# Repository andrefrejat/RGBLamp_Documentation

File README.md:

# RGBLamp_Documentation
RGB Lamp made beggining 2015. The base is an arduino Uno. Software and hardware explanation on the video (in portuguese).

The project works in three different forms:
1) Red green and blue lights alternate
2) The ammount of Red Green and Blue on the light is controlled by three potentiometers on the side
3) The color is controlled via computer software.

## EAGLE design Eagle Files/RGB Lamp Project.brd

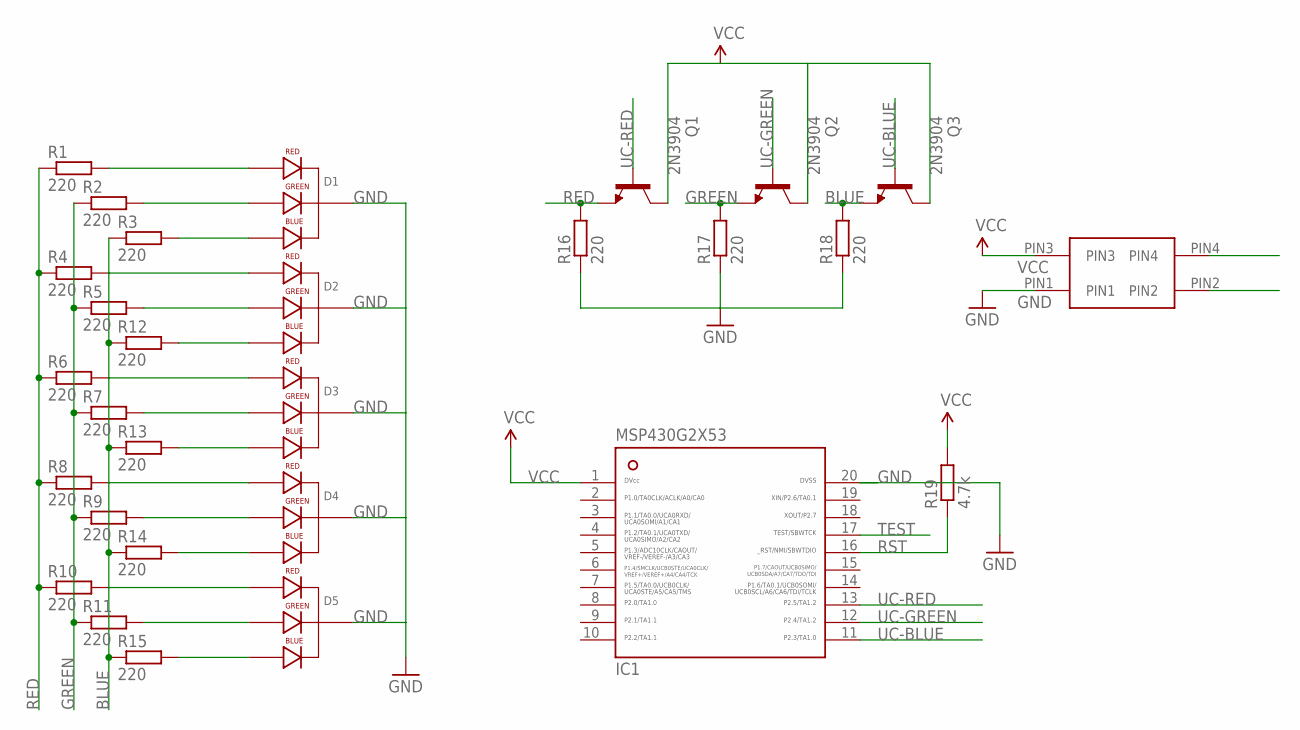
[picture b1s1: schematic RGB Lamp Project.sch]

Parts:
D1, D2, D3, D4, D5: LED-RGB-CC-THRUCLEAR; LED-RGB-THRU
IC1: MSP430G2X53-20PW20; PW20
Q1, Q2, Q3: 2N3904; TO92
R1, R2, R3, R4, R5, R6, R7, R8, R9, R10, R11, R12, R13, R14, R15, R16, R17, R18: 220; R0805
R19: 4.7k; R0805
U$1: PINHEADER-2X2-SMD

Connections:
BLUE: Q3.3 (E), R3.1, R12.1, R13.1, R14.1, R15.1, R18.2
GND: D1.2 (CATHODE), D2.2 (CATHODE), D3.2 (CATHODE), D4.2 (CATHODE), D5.2 (CATHODE), IC1.20, R16.1, R17.1, R18.1, U$1.PIN1
GREEN: Q2.3 (E), R2.1, R5.1, R7.1, R9.1, R11.1, R17.2
unnamed: D1.1 (RED_CATHODE), R1.2
unnamed: D1.3 (GREEN_CATHODE), R2.2
unnamed: D1.4 (BLUE_CATHODE), R3.2
unnamed: D2.1 (RED_CATHODE), R4.2
unnamed: D2.3 (GREEN_CATHODE), R5.2
unnamed: D2.4 (BLUE_CATHODE), R12.2
unnamed: D3.1 (RED_CATHODE), R6.2
unnamed: D3.3 (GREEN_CATHODE), R7.2
unnamed: D3.4 (BLUE_CATHODE), R13.2
unnamed: D4.1 (RED_CATHODE), R8.2
unnamed: D4.3 (GREEN_CATHODE), R9.2
unnamed: D4.4 (BLUE_CATHODE), R14.2
unnamed: D5.1 (RED_CATHODE), R10.2
unnamed: D5.4 (BLUE_CATHODE), R15.2
unnamed: D5.3 (GREEN_CATHODE), R11.2
RED: Q1.3 (E), R1.1, R4.1, R6.1, R8.1, R10.1, R16.2
RST: IC1.16, R19.1, U$1.PIN4
TEST: IC1.17, U$1.PIN2
UC-BLUE: IC1.11, Q3.2 (B)
UC-GREEN: IC1.12, Q2.2 (B)
UC-RED: IC1.13, Q1.2 (B)
VCC: IC1.1, Q1.1 (C), Q2.1 (C), Q3.1 (C), R19.2, U$1.PIN3

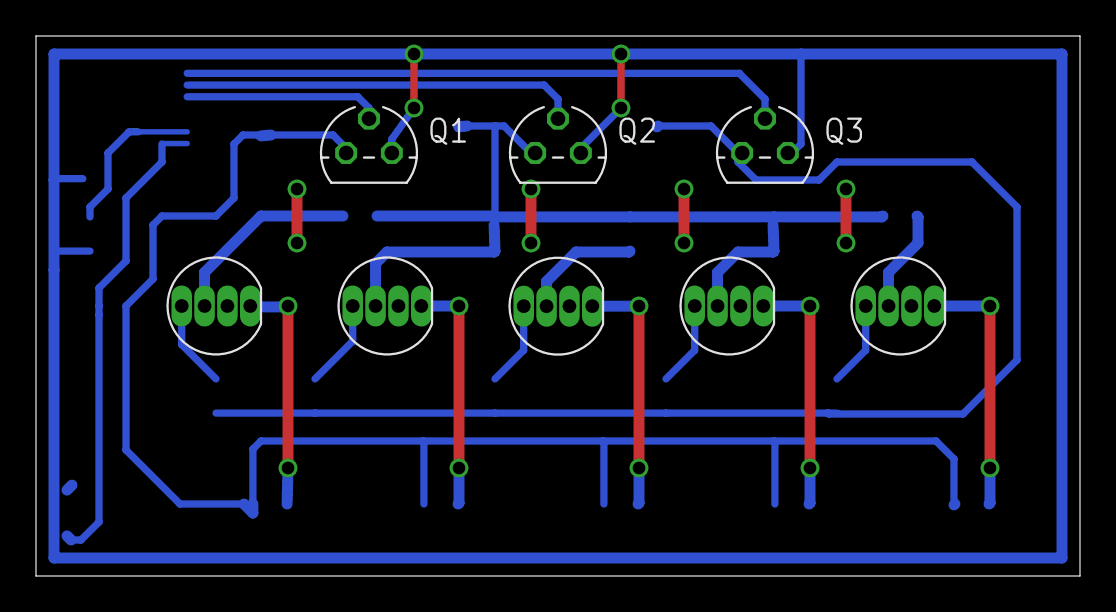
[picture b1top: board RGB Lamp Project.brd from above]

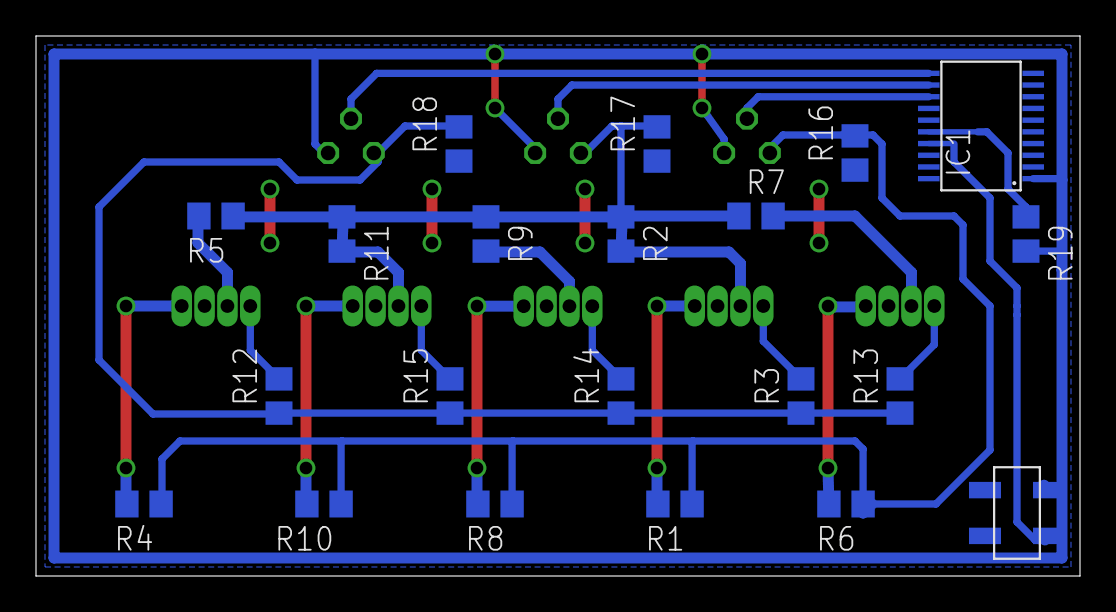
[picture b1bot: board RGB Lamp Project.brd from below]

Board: 2 copper layers, 58.0 x 30.0 mm, 29 parts (21 on the bottom side), 25 nets.

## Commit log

2016-11-11 Added Files
2016-11-11 Added eagle files

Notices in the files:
parts and their libraries:
SparkFun-LED: Licensing: Creative Commons ShareAlike 4.0 International - https://creativecommons.org/licenses/by-sa/4.0
